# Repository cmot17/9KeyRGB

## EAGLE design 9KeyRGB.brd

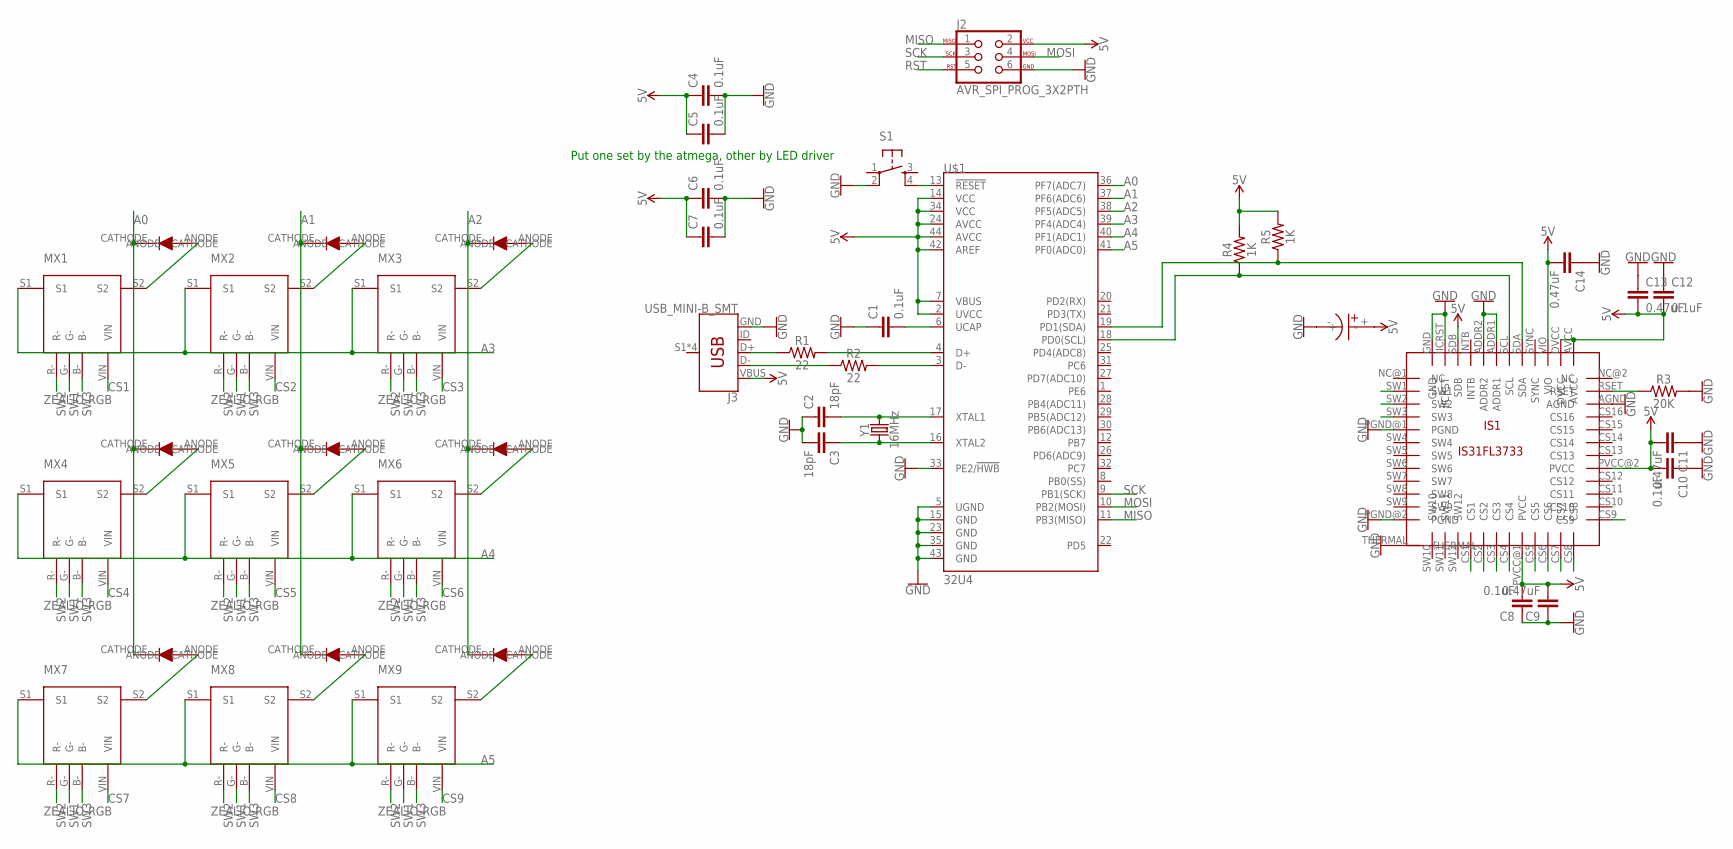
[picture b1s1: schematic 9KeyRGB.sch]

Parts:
C1, C4, C5, C6, C7, C8, C10, C12: 0.1uF; 0603
C2, C3: 18pF; 0603
C9, C11, C13, C14: 0.47uF; 0603
D1, D2, D3, D4, D5, D6, D7, D8, D9: BAS16L
IS1: IS31FL3733
J2: AVR_SPI_PROG_3X2PTH; 2X3
J3: USB_MINI-B_SMT; USB-MINIB
MX1, MX2, MX3, MX4, MX5, MX6, MX7, MX8, MX9: ZEALIO-RGB
R1, R2: 22; 0603
R3: 20K; 0603
R4, R5: 1K; 0603
S1: TAC_SWITCHPTH; TACTILE-PTH
U$1: 32U4; TQFP44
U$2: EEA-FC1A220
Y1: 16MHz; HC49US

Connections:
5V: C4.1, C5.1, C6.1, C7.1, C8.2, C9.2, C10.2, C11.2, C12.2, C13.2, C14.2, IS1.AVCC, IS1.DVCC, IS1.PVCC@1 (PVCC), IS1.PVCC@2 (PVCC), IS1.SDB, IS1.VIO, J2.2, J3.VBUS, R4.2, R5.2, U$1.2 (UVCC), U$1.7 (VBUS), U$1.14 (VCC), U$1.24 (AVCC), U$1.34 (VCC), U$1.42 (AREF), U$1.44 (AVCC), U$2.+
A0: D1.CATHODE, D4.CATHODE, D7.CATHODE, U$1.36 (PF7(ADC7))
A1: D2.CATHODE, D5.CATHODE, D8.CATHODE, U$1.37 (PF6(ADC6))
A2: D3.CATHODE, D6.CATHODE, D9.CATHODE, U$1.38 (PF5(ADC5))
A3: MX1.S1, MX2.S1, MX3.S1, U$1.39 (PF4(ADC4))
A4: MX4.S1, MX5.S1, MX6.S1, U$1.40 (PF1(ADC1))
A5: MX7.S1, MX8.S1, MX9.S1, U$1.41 (PF0(ADC0))
CS1: IS1.CS1, MX1.VIN
CS2: IS1.CS2, MX2.VIN
CS3: IS1.CS3, MX3.VIN
CS4: IS1.CS4, MX4.VIN
CS5: IS1.CS5, MX5.VIN
CS6: IS1.CS6, MX6.VIN
CS7: IS1.CS7, MX7.VIN
CS8: IS1.CS8, MX8.VIN
CS9: IS1.CS9, MX9.VIN
GND: C1.1, C2.1, C3.2, C4.2, C5.2, C6.2, C7.2, C8.1, C9.1, C10.1, C11.1, C12.1, C13.1, C14.1, IS1.ADDR1, IS1.ADDR2, IS1.AGND, IS1.GND, IS1.IICRST, IS1.PGND@1 (PGND), IS1.PGND@2 (PGND), IS1.THERMAL, J2.6, J3.GND, R3.2, S1.2, U$1.5 (UGND), U$1.15 (GND), U$1.23 (GND), U$1.33 (PE2/!HWB), U$1.35 (GND), U$1.43 (GND), U$2.-
MISO: J2.1, U$1.11 (PB3(MISO))
MOSI: J2.4, U$1.10 (PB2(MOSI))
unnamed: D1.ANODE, MX1.S2
unnamed: D2.ANODE, MX2.S2
unnamed: D3.ANODE, MX3.S2
unnamed: D4.ANODE, MX4.S2
unnamed: D5.ANODE, MX5.S2
unnamed: D6.ANODE, MX6.S2
unnamed: D7.ANODE, MX7.S2
unnamed: D8.ANODE, MX8.S2
unnamed: D9.ANODE, MX9.S2
unnamed: IS1.SDA, R5.1, U$1.19 (PD1(SDA))
unnamed: C1.2, U$1.6 (UCAP)
unnamed: J3.D+, R1.1
unnamed: R1.2, U$1.4 (D+)
unnamed: J3.D-, R2.1
unnamed: R2.2, U$1.3 (D-)
unnamed: C2.2, U$1.17 (XTAL1), Y1.2
unnamed: C3.1, U$1.16 (XTAL2), Y1.1
unnamed: IS1.SCL, R4.1, U$1.18 (PD0(SCL))
unnamed: IS1.RSET, R3.1
RST: J2.5, S1.4, U$1.13 (!RESET)
SCK: J2.3, U$1.9 (PB1(SCK))
SW1: IS1.SW1, MX1.G-, MX2.G-, MX3.G-, MX4.G-, MX5.G-, MX6.G-, MX7.G-, MX8.G-, MX9.G-
SW2: IS1.SW2, MX1.R-, MX2.R-, MX3.R-, MX4.R-, MX5.R-, MX6.R-, MX7.R-, MX8.R-, MX9.R-
SW3: IS1.SW3, MX1.B-, MX2.B-, MX3.B-, MX4.B-, MX5.B-, MX6.B-, MX7.B-, MX8.B-, MX9.B-

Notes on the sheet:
Put one set by the atmega, other by LED driver

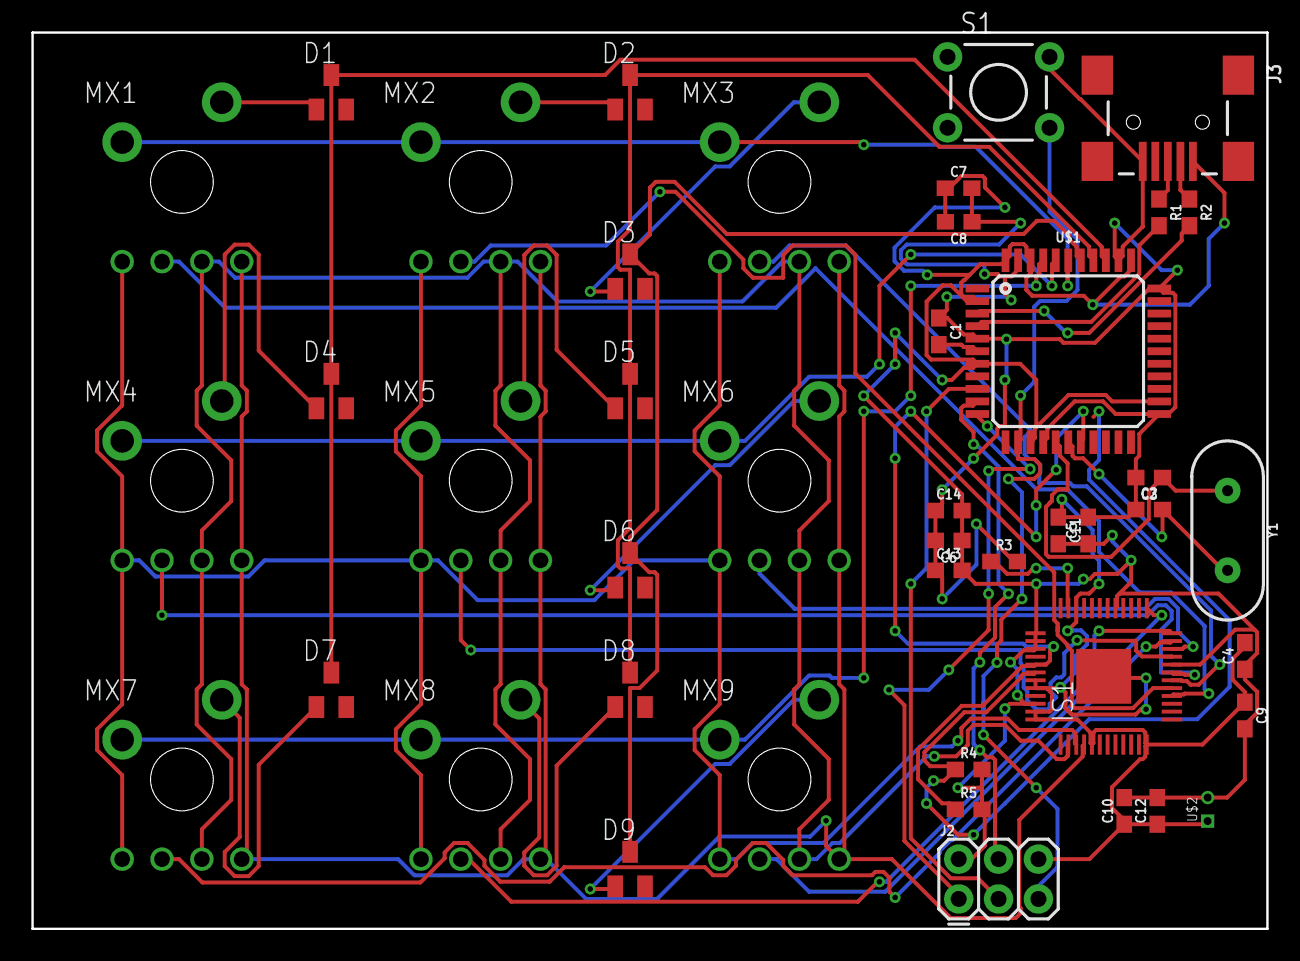
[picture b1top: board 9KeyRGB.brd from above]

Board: 2 copper layers, 78.7 x 57.1 mm, 44 parts (0 on the bottom side), 43 nets.

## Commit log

2018-02-09 Rename 9KeyRGBSchematic.sch to 9KeyRGB.sch

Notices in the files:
parts and their libraries:
SparkFun-IC-Microcontroller: Licensing: Creative Commons ShareAlike 4.0 International - https://creativecommons.org/licenses/by-sa/4.0
